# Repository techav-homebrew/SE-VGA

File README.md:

# SE-VGA
SE-VGA is a video card primarily for the Mac SE, but also compatible with the Macintosh, 512k, and Plus. The FPGA configuration here will duplicate the Mac video pixel-doubled to 1024x768 and displayed letterboxed (black borders) in a 1024x768@60Hz frame over VGA. It does this by snooping the CPU bus for writes to the frame buffer region of memory, caching the video data in its own VRAM, and generating a new video signal from that data. It can plug directly into the PDS slot in a Mac SE, or plugs in place of the CPU on the Plus, 512k, or 128k models (CPU must be removed and a socket installed in its place; the CPU must then be installed on the SE-VGA card).

Circuit is built around a Latice iCE40HX4K FPGA with a single 16-bit SDRAM, theoretically supporting up to 512Mbit (64MB) of video memory. Video output is a 24-bit R2R DAC with output buffer. The PCB is designed as a 4-layer board with inner power and ground planes. Use of a PCB assembly service is recommended for the many 0402 passive components. 

The memory capacity and output capabilities of this project greatly exceed those necessary for duplicating the classic Macintosh video output in the hopes that it may be a starting point for projects which go beyond merely duplicating the classic Macintosh video output.

## Bill of Materials

| Qty | Manufacturer    | Part No.           | Name               | Description                                   |
|:---:|:----------------|:-------------------|:-------------------|:----------------------------------------------|
|     |                 |                    |                    |                                               | 

## Frame Buffer Addressing

The Mac primary framebuffer starts at 0x5900 below the top of RAM. Since it's not in a static location for every system, the system's memory configuration is needed. This is set by the Memory Size switches/jumpers. The chart below indicates the primary and alternate frame buffer locations based on the installed SIMM combinations in the Mac Plus/SE, as well as for the 512k & 128k models. 

|Main Framebuffer|Alt Framebuffer|RAM Top Address + 1|RAM Size|Installed SIMMs               |
|:--------------:|:-------------:|:-----------------:|:------:|------------------------------|
| `0x3fa700`     | `0x3f2700`    | `0x400000`        | 4.0MB  | `[ 1MB   1MB ][ 1MB   1MB ]` |
| `0x37a700`     | `0x372700`    | `0x380000`        | 3.5MB  | Invalid combination          |
| `0x2fa700`     | `0x2f2700`    | `0x300000`        | 3.0MB  | Invalid combination          |
| `0x27a700`     | `0x272700`    | `0x280000`        | 2.5MB  | `[ 1MB   1MB ][256kB 256kB]` |
| `0x1fa700`     | `0x1f2700`    | `0x200000`        | 2.0MB  | `[ 1MB   1MB ][ ---   --- ]` |
| `0x17a700`     | `0x172700`    | `0x180000`        | 1.5MB  | Invalid combination          |
| `0x0fa700`     | `0x0f2700`    | `0x100000`        | 1.0MB  | `[256kB 256kB][256kB 256kB]` |
| `0x07a700`     | `0x072700`    | `0x080000`        | 512kB  | `[256kB 256kB][ ---   --- ]` |
| `0x01a700`     | `0x012700`    | `0x020000`        | 128kB  | NA                           |

## FPGA Pin Assignments

|signal|Direction|Pin|
|---|---|---|
|   |   |   |

## Known Issues
- Logic has not yet been rewritten for the iCE40 FPGA

# License
This work is licensed under a Creative Commons Attribution-ShareAlike 4.0 International License. See https://creativecommons.org/licenses/by-sa/4.0/.

# Acknowledgements
Special thanks to TubeTimeUS, whose Graphics Gremlin project answered many of the questions I had while designing this project. 
https://github.com/schlae/graphics-gremlin

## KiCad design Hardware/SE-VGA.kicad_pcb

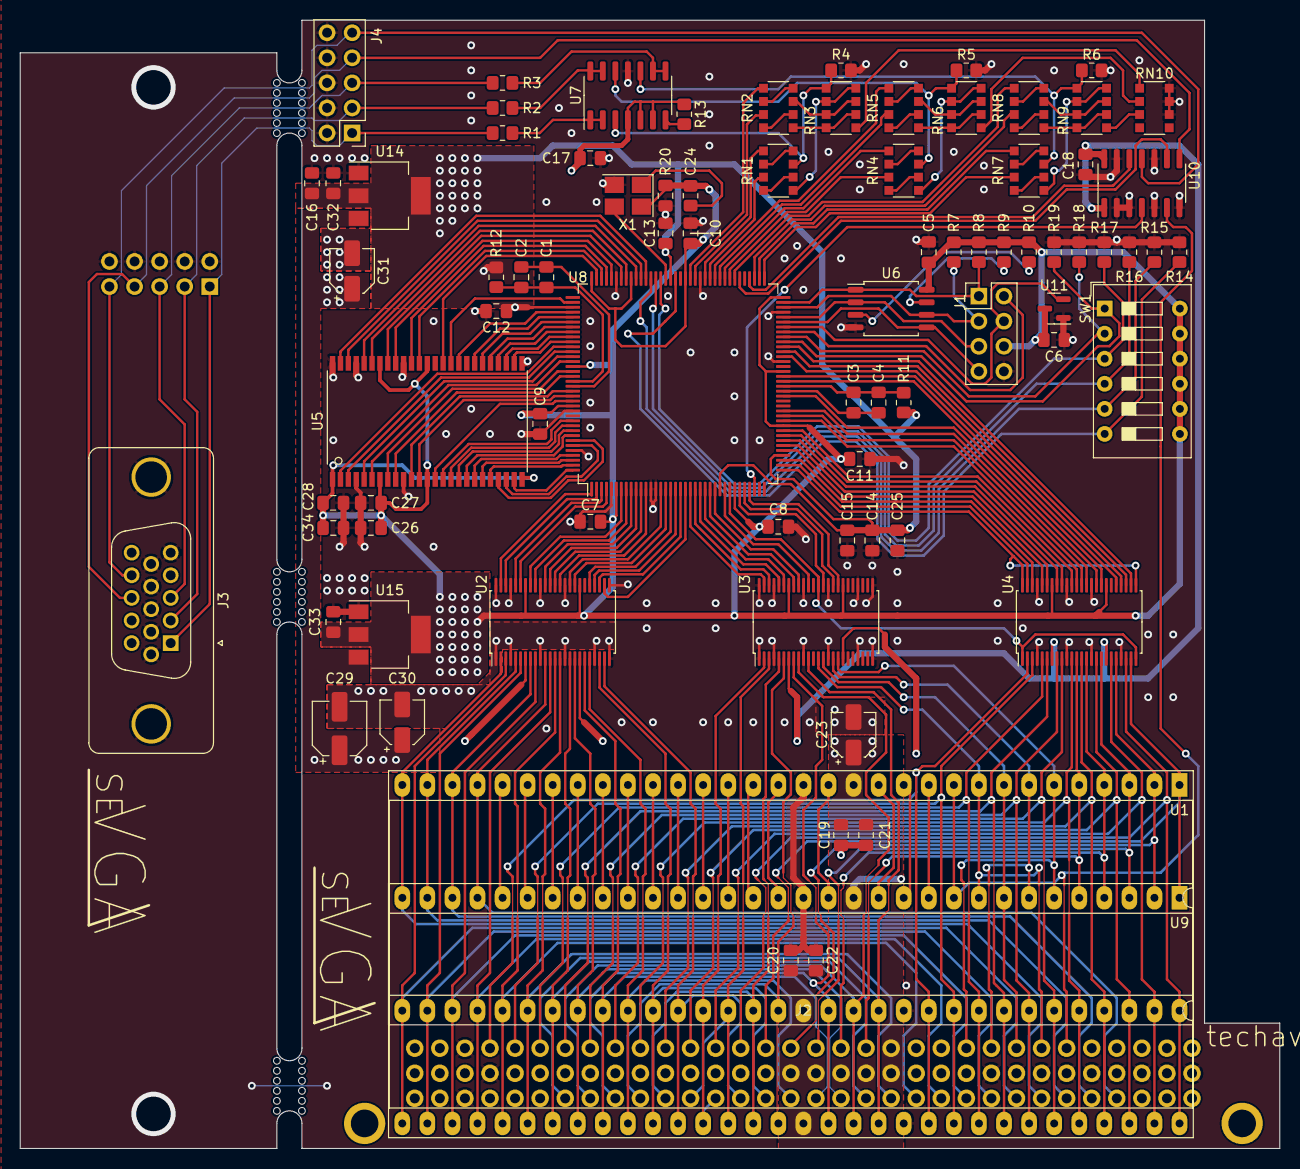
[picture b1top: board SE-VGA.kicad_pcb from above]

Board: 2 copper layers, 127.6 x 114.3 mm, 84 parts (1 on the bottom side), 215 nets.

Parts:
C1, C3, C5, C6, C7, C8, C9, C10, C13, C14, C15, C16, C17, C18, C19, C20, C24, C27, C28: 1uF; C_0805_2012Metric_Pad1.18x1.45mm_HandSolder
C2, C4, C11, C12, C21, C22, C25, C26, C32, C33, C34: 4.7uF; C_0805_2012Metric_Pad1.18x1.45mm_HandSolder
C23, C30, C31: 10uF; CP_Elec_4x5.3
C29: 100uF; CP_Elec_5x5.4
J1: PGM; PinHeader_2x04_P2.54mm_Vertical
J2: 650946-5; DIN41612-32ABC
J3: DE15_Receptacle_HighDensity_MountingHoles; DSUB-15-HD_Female_Vertical_P2.29x1.98mm_MountingHoles
J4, J5: Conn_02x05_Odd_Even; PinHeader_2x05_P2.54mm_Vertical
R1, R2, R3, R4, R5, R6, R13: 75R; R_0805_2012Metric_Pad1.20x1.40mm_HandSolder
R7, R8, R9, R10, R14, R15, R16, R17, R18, R19, R20: 10K; R_0805_2012Metric_Pad1.20x1.40mm_HandSolder
R11, R12: 100; R_0805_2012Metric_Pad1.20x1.40mm_HandSolder
RN1, RN2, RN3, RN4, RN5, RN6, RN7, RN8, RN9, RN10: CAY16-1500F4LF; R_Array_Convex_4x1206
SW1: SW_DIP_x06; SW_DIP_SPSTx06_Slide_9.78x17.42mm_W7.62mm_P2.54mm
U1: 68000-CPU; DIP-64_W22.86mm_Socket_LongPads
U2, U3, U4: SN74LVCH16T245; TSSOP-48_6.1x12.5mm_P0.5mm
U5: IS42S16100H; TSOP2-50
U6: W25Q80DVSNIG; SOIC-8_5.275x5.275mm_P1.27mm
U7: ADA4891-4; SOIC-14_3.9x8.7mm_P1.27mm
U8: ICE40HX4K-TQ144; TQFP-144_20x20mm_P0.5mm
U9: 68000-BOARD; DIP-64_W22.86mm_Socket_LongPads
U10: 74HCT125D; SOIC-14_3.9x8.7mm_P1.27mm
U11: APX803S00-29SA-7; SOT-23
U14: AZ1117IH-1.2TRG1; SOT-223-3_TabPin2
U15: AZ1117IH-3.3TRG1; SOT-223-3_TabPin2
X1: ECS-2333-100-BN-TR; Oscillator_SMD_Abracon_ASE-4Pin_3.2x2.5mm_HandSoldering

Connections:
+1V2: C12.2, C13.2, C14.2, C15.2, C16.2, C25.2, C32.2, R11.2, R12.2, U8.27 (VCC), U8.40 (VCC), U8.92 (VCC), U8.111 (VCC), U14.2 (VO)
+3V3: C5.2, C6.2, C7.2, C8.2, C9.2, C10.2, C11.2, C24.1, C26.2, C27.2, C28.2, C33.2, C34.2, J1.6, R7.2, R8.2, R9.2, R10.2, R20.2, SW1.7, SW1.8, SW1.9, SW1.10, SW1.11, SW1.12, U2.31 (VCCA), U2.42 (VCCA), U3.31 (VCCA), U3.42 (VCCA), U4.31 (VCCA), U4.42 (VCCA), U5.1 (VDD), U5.7 (VDDQ), U5.13 (VDDQ), U5.25 (VDD), U5.38 (VDDQ), U5.44 (VDDQ), U6.8 (VDD), U8.6 (VCCIO_3), U8.30 (VCCIO_3), U8.46 (VCCIO_2), U8.57 (VCCIO_2), U8.72 (VCC_SPI), U8.89 (VCCIO_1), U8.100 (VCCIO_1), U8.108 (VPP_2V5), U8.123 (VCCIO_0), U8.131 (VCCIO_0), U11.3 (VCC), U15.2 (VO), X1.4 (VDD)
+5V: C17.2, C18.2, C19.2, C20.2, C21.2, C22.2, C23.1, C29.1, C30.1, C31.1, J2.B13, J2.B14, J2.B15, J2.B16, J2.B17, J2.C13, R13.1, U1.14 (VCC), U1.49 (VCC), U2.7 (VCCB), U2.18 (VCCB), U3.7 (VCCB), U3.18 (VCCB), U4.7 (VCCB), U4.18 (VCCB), U7.4 (VCC), U7.5 (IN2_P), U7.6 (IN2_N), U9.14 (VCC), U9.49 (VCC), U10.1, U10.14 (VCC), U14.3 (VI), U15.3 (VI)
/AUXSW: R14.2, SW1.6, U8.91 (IOR_139)
/CBSEL0: R19.2, SW1.1, U8.63 (IOB_103_CBSEL0)
/CBSEL1: R18.2, SW1.2, U8.64 (IOB_104_CBSEL1)
/CLK-10M: U8.93 (IOR_140_GBIN3), X1.3 (OUT)
/CPU3-A1: U2.38 (1A7), U8.9 (IOL_5A)
/CPU3-A2: U2.41 (1A5), U8.7 (IOL_4A)
/CPU3-A3: U2.44 (1A3), U8.3 (IOL_3A)
/CPU3-A4: U2.47 (1A1), U8.1 (IOL_2A)
/CPU3-A5: U2.46 (1A2), U8.2 (IOL_2B)
/CPU3-A6: U2.43 (1A4), U8.4 (IOL_3B)
/CPU3-A7: U2.40 (1A6), U8.8 (IOL_4B)
/CPU3-A8: U2.37 (1A8), U8.10 (IOL_5B)
/CPU3-A9: U2.36 (2A1), U8.11 (IOL_8A)
/CPU3-A10: U2.35 (2A2), U8.12 (IOL_8B)
/CPU3-A11: U2.33 (2A3), U8.15 (IOL_10A)
/CPU3-A12: U2.32 (2A4), U8.16 (IOL_10B)
/CPU3-A13: U2.28 (2A5), U8.18 (IOL_12B)
/CPU3-A14: U2.29 (2A6), U8.17 (IOL_12A)
/CPU3-A15: U2.27 (2A7), U8.19 (IOL_13A)
/CPU3-A16: U2.26 (2A8), U8.20 (IOL_13B_GBIN7)
/CPU3-A17: U3.47 (1A1), U8.21 (IOL_14A_GBIN6)
/CPU3-A18: U3.46 (1A2), U8.22 (IOL_14B)
/CPU3-A19: U3.44 (1A3), U8.23 (IOL_17A)
/CPU3-A20: U3.43 (1A4), U8.24 (IOL_17B)
/CPU3-A21: U3.41 (1A5), U8.25 (IOL_18A)
/CPU3-A22: U3.40 (1A6), U8.26 (IOL_18B)
/CPU3-A23: U3.38 (1A7), U8.28 (IOL_23A)
/CPU3-D0: U4.37 (1A8), U8.47 (IOB_79)
/CPU3-D1: U4.35 (2A2), U8.49 (IOB_81_GBIN5)
/CPU3-D2: U4.32 (2A4), U8.55 (IOB_91)
/CPU3-D3: U4.29 (2A6), U8.56 (IOB_94)
/CPU3-D4: U4.26 (2A8), U8.62 (IOB_102)
/CPU3-D5: U4.27 (2A7), U8.61 (IOB_96)
/CPU3-D6: U4.28 (2A5), U8.60 (IOB_95)
/CPU3-D7: U4.33 (2A3), U8.52 (IOB_82_GBIN4)
/CPU3-D8: U4.36 (2A1), U8.48 (IOB_80)
/CPU3-D9: U4.38 (1A7), U8.45 (IOB_73)
/CPU3-D10: U4.40 (1A6), U8.44 (IOB_72)
/CPU3-D11: U4.41 (1A5), U8.43 (IOB_71)
/CPU3-D12: U4.43 (1A4), U8.42 (IOB_64)
/CPU3-D13: U4.44 (1A3), U8.41 (IOB_63)
/CPU3-D14: U4.46 (1A2), U8.39 (IOB_61)
/CPU3-D15: U4.47 (1A1), U8.38 (IOB_57)
/CPU3-R/~W: U3.36 (2A1), U4.1 (1DIR), U4.24 (2DIR), U8.29 (IOL_23B)
/MEMSEL0: R17.2, SW1.3, U8.94 (IOR_141_GBIN2)
/MEMSEL1: R16.2, SW1.4, U8.95 (IOR_144)
/MEMSEL2: R15.2, SW1.5, U8.96 (IOR_146)
/Mac Interface/CPU-A1: J2.A4, U1.29 (A1), U2.11 (1B7), U9.29 (A1)
/Mac Interface/CPU-A2: J2.A5, U1.30 (A2), U2.8 (1B5), U9.30 (A2)
/Mac Interface/CPU-A3: J2.A6, U1.31 (A3), U2.5 (1B3), U9.31 (A3)
/Mac Interface/CPU-A4: J2.A7, U1.32 (A4), U2.2 (1B1), U9.32 (A4)
/Mac Interface/CPU-A5: J2.A8, U1.33 (A5), U2.3 (1B2), U9.33 (A5)
/Mac Interface/CPU-A6: J2.A9, U1.34 (A6), U2.6 (1B4), U9.34 (A6)
/Mac Interface/CPU-A7: J2.A10, U1.35 (A7), U2.9 (1B6), U9.35 (A7)
/Mac Interface/CPU-A8: J2.A11, U1.36 (A8), U2.12 (1B8), U9.36 (A8)
/Mac Interface/CPU-A9: J2.A12, U1.37 (A9), U2.13 (2B1), U9.37 (A9)
/Mac Interface/CPU-A10: J2.A13, U1.38 (A10), U2.14 (2B2), U9.38 (A10)
/Mac Interface/CPU-A11: J2.A14, U1.39 (A11), U2.16 (2B3), U9.39 (A11)
/Mac Interface/CPU-A12: J2.A15, U1.40 (A12), U2.17 (2B4), U9.40 (A12)
/Mac Interface/CPU-A13: J2.A16, U1.41 (A13), U2.19 (2B5), U9.41 (A13)
/Mac Interface/CPU-A14: J2.A17, U1.42 (A14), U2.20 (2B6), U9.42 (A14)
/Mac Interface/CPU-A15: J2.A18, U1.43 (A15), U2.22 (2B7), U9.43 (A15)
/Mac Interface/CPU-A16: J2.A19, U1.44 (A16), U2.23 (2B8), U9.44 (A16)
/Mac Interface/CPU-A17: J2.A20, U1.45 (A17), U3.2 (1B1), U9.45 (A17)
/Mac Interface/CPU-A18: J2.A21, U1.46 (A18), U3.3 (1B2), U9.46 (A18)
/Mac Interface/CPU-A19: J2.A22, U1.47 (A19), U3.5 (1B3), U9.47 (A19)
/Mac Interface/CPU-A20: J2.A23, U1.48 (A20), U3.6 (1B4), U9.48 (A20)
/Mac Interface/CPU-A21: J2.A24, U1.50 (A21), U3.8 (1B5), U9.50 (A21)
/Mac Interface/CPU-A22: J2.A25, U1.51 (A22), U3.9 (1B6), U9.51 (A22)
/Mac Interface/CPU-A23: J2.A26, U1.52 (A23), U3.11 (1B7), U9.52 (A23)
/Mac Interface/CPU-CLK: U1.15 (CLK), U9.15 (CLK)
/Mac Interface/CPU-D0: J2.C14, U1.5 (D0), U4.12 (1B8), U9.5 (D0)
/Mac Interface/CPU-D1: J2.C15, U1.4 (D1), U4.14 (2B2), U9.4 (D1)
/Mac Interface/CPU-D2: J2.C16, U1.3 (D2), U4.17 (2B4), U9.3 (D2)
/Mac Interface/CPU-D3: J2.C17, U1.2 (D3), U4.20 (2B6), U9.2 (D3)
/Mac Interface/CPU-D4: J2.C18, U1.1 (D4), U4.23 (2B8), U9.1 (D4)
/Mac Interface/CPU-D5: J2.C19, U1.64 (D5), U4.22 (2B7), U9.64 (D5)
/Mac Interface/CPU-D6: J2.C20, U1.63 (D6), U4.19 (2B5), U9.63 (D6)
/Mac Interface/CPU-D7: J2.C21, U1.62 (D7), U4.16 (2B3), U9.62 (D7)
/Mac Interface/CPU-D8: J2.C22, U1.61 (D8), U4.13 (2B1), U9.61 (D8)
/Mac Interface/CPU-D9: J2.C23, U1.60 (D9), U4.11 (1B7), U9.60 (D9)
/Mac Interface/CPU-D10: J2.C24, U1.59 (D10), U4.9 (1B6), U9.59 (D10)
/Mac Interface/CPU-D11: J2.C25, U1.58 (D11), U4.8 (1B5), U9.58 (D11)
/Mac Interface/CPU-D12: J2.C26, U1.57 (D12), U4.6 (1B4), U9.57 (D12)
/Mac Interface/CPU-D13: J2.C27, U1.56 (D13), U4.5 (1B3), U9.56 (D13)
/Mac Interface/CPU-D14: J2.C28, U1.55 (D14), U4.3 (1B2), U9.55 (D14)
/Mac Interface/CPU-D15: J2.C29, U1.54 (D15), U4.2 (1B1), U9.54 (D15)
/Mac Interface/CPU-E: U1.20 (E), U9.20 (E)
/Mac Interface/CPU-FC0: U1.28 (FC0), U9.28 (FC0)
/Mac Interface/CPU-FC1: U1.27 (FC1), U9.27 (FC1)
/Mac Interface/CPU-FC2: U1.26 (FC2), U9.26 (FC2)
/Mac Interface/CPU-R/~W: J2.C7, U1.9 (R/W), U3.13 (2B1), U9.9 (R/W)
/Mac Interface/~CPU-AS: J2.C10, U1.6 (AS), U3.17 (2B4), U9.6 (AS)
/Mac Interface/~CPU-BERR: U1.22 (BERR), U9.22 (BERR)
/Mac Interface/~CPU-BGACK: U1.12 (BGACK), U9.12 (BGACK)
/Mac Interface/~CPU-BG: U1.11 (BG), U9.11 (BG)
/Mac Interface/~CPU-BR: U1.13 (BR), U9.13 (BR)
/Mac Interface/~CPU-HALT: U1.17 (HALT), U9.17 (HALT)
/Mac Interface/~CPU-IPL0: U1.25 (IPL0), U9.25 (IPL0)
/Mac Interface/~CPU-IPL1: U1.24 (IPL1), U9.24 (IPL1)
/Mac Interface/~CPU-IPL2: U1.23 (IPL2), U9.23 (IPL2)
/Mac Interface/~CPU-LDS: J2.C8, U1.8 (LDS), U3.14 (2B2), U9.8 (LDS)
/Mac Interface/~CPU-RESET: U1.18 (RESET), U9.18 (RESET)
/Mac Interface/~CPU-UDS: J2.C9, U1.7 (UDS), U3.16 (2B3), U9.7 (UDS)
/Mac Interface/~CPU-VMA: U1.19 (VMA), U9.19 (VMA)
/Mac Interface/~CPU-VPA: U1.21 (VPA), U9.21 (VPA)
/SPI_SCK: J1.3, R7.1, U6.6 (SCK), U8.70 (IOB_107_SCK)
/SPI_SDI: J1.5, U6.2 (SO), U8.68 (IOB_106_SDI)
/SPI_SDO: J1.7, U6.5 (SI), U8.67 (IOB_105_SDO)
/SPI_SS: J1.1, R8.1, U6.1 (~CE), U8.71 (IOB_108_SS)
/VID-B0: RN8.3 (R3.1), U8.75 (IOR_111)
/VID-B1: RN8.1 (R1.1), U8.79 (IOR_115)
/VID-B2: RN7.3 (R3.1), U8.73 (IOR_109)
/VID-B3: RN7.1 (R1.1), U8.74 (IOR_110)
/VID-B-A: J3.3, J4.5, J5.5, R3.2
/VID-G0: RN5.3 (R3.1), U8.82 (IOR_118)
/VID-G1: RN5.1 (R1.1), U8.83 (IOR_119)
/VID-G2: RN4.3 (R3.1), U8.80 (IOR_116)
/VID-G3: RN4.1 (R1.1), U8.81 (IOR_117)
/VID-G-A: J3.2, J4.3, J5.3, R2.2
/VID-HSYNC: J3.13, J4.7, J5.7, U10.8
/VID-HSYNC3: U8.78 (IOR_114), U10.9
/VID-R0: RN2.3 (R3.1), U8.87 (IOR_136)
/VID-R1: RN2.1 (R1.1), U8.88 (IOR_137)
/VID-R2: RN1.3 (R3.1), U8.84 (IOR_120)
/VID-R3: RN1.1 (R1.1), U8.85 (IOR_128)
/VID-R-A: J3.1, J4.1, J5.1, R1.2
/VID-VSYNC: J3.14, J4.9, J5.9, U10.11
/VID-VSYNC3: U8.76 (IOR_112), U10.12
/VRAM-A0: U5.21 (A0), U8.143 (IOT_221)
/VRAM-A1: U5.22 (A1), U8.138 (IOT_216)
/VRAM-A2: U5.23 (A2), U8.139 (IOT_217)
/VRAM-A3: U5.24 (A3), U8.144 (IOT_222)
/VRAM-A4: U5.27 (A4), U8.118 (IOT_177)
/VRAM-A5: U5.28 (A5), U8.117 (IOT_174)
/VRAM-A6: U5.29 (A6), U8.116 (IOT_173)
/VRAM-A7: U5.30 (A7), U8.115 (IOT_172)
/VRAM-A8: U5.31 (A8), U8.114 (IOT_171)
/VRAM-A9: U5.32 (A9), U8.113 (IOT_170)
/VRAM-A10: U5.20 (A10), U8.142 (IOT_220)
/VRAM-A11: U5.19 (A11), U8.141 (IOT_219)
/VRAM-CKE: U5.34 (CKE), U8.112 (IOT_169)
/VRAM-CLK: U5.35 (CLK), U8.110 (IOT_168)
/VRAM-D0: U5.2 (DQ0), U8.119 (IOT_178)
/VRAM-D1: U5.3 (DQ1), U8.120 (IOT_179)
/VRAM-D2: U5.5 (DQ2), U8.121 (IOT_181)
/VRAM-D3: U5.6 (DQ3), U8.122 (IOT_190)
/VRAM-D4: U5.8 (DQ4), U8.124 (IOT_191)
/VRAM-D5: U5.9 (DQ5), U8.125 (IOT_192)
/VRAM-D6: U5.11 (DQ6), U8.128 (IOT_197_GBIN1)
/VRAM-D7: U5.12 (DQ7), U8.129 (IOT_198_GBIN0)
/VRAM-D8: U5.39 (DQ8), U8.106 (IOR_166)
/VRAM-D9: U5.40 (DQ9), U8.105 (IOR_165)
/VRAM-D10: U5.42 (DQ10), U8.104 (IOR_164)
/VRAM-D11: U5.43 (DQ11), U8.102 (IOR_161)
/VRAM-D12: U5.45 (DQ12), U8.101 (IOR_160)
/VRAM-D13: U5.46 (DQ13), U8.99 (IOR_152)
/VRAM-D14: U5.48 (DQ14), U8.98 (IOR_148)
/VRAM-D15: U5.49 (DQ15), U8.97 (IOR_147)
/VRAM-LDQM: U5.14 (LDQM), U8.130 (IOT_206)
/VRAM-UDQM: U5.36 (UDQM), U8.107 (IOR_167)
/~CDONE: J1.2, U8.65 (CDONE)
/~CPU3-AS: U3.32 (2A4), U8.33 (IOL_25A)
/~CPU3-DEN: U4.25 (~2OE), U4.48 (~1OE), U8.37 (IOB_56)
/~CPU3-DTACK: U8.34 (IOL_25B), U10.4
/~CPU3-LDS: U3.35 (2A2), U8.31 (IOL_24A)
/~CPU3-UDS: U3.33 (2A3), U8.32 (IOL_24B)
/~CPU-DTACK: J2.C6, U1.10 (DTACK), U9.10 (DTACK), U10.6
/~CRESET: J1.4, U8.66 (~CRESET), U11.2 (~RESET)
/~VRAM-CAS: U5.16 (~CAS), U8.135 (IOT_213)
/~VRAM-CS: U5.18 (~CS), U8.137 (IOT_215)
/~VRAM-RAS: U5.17 (~RAS), U8.136 (IOT_214)
/~VRAM-WE: U5.15 (~WE), U8.134 (IOT_212)
GND: C5.1, C6.1, C7.1, C8.1, C9.1, C10.1, C11.1, C12.1, C13.1, C14.1, C15.1, C16.1, C17.1, C18.1, C19.1, C20.1, C21.1, C22.1, C23.2, C24.2, C25.1, C26.1, C27.1, C28.1, C29.2, C30.2, C31.2, C32.1, C33.1, C34.1, J1.8, J2.A30, J2.B1, J2.B2, J2.B3, J2.B4, J2.B5, J2.B6, J2.B7, J2.B8, J2.B9, J2.B29, J2.C30, J3.0, J3.5, J3.6, J3.7, J3.8, J3.9, J3.10, J4.2, J4.4, J4.6, J4.8, J4.10, J5.2, J5.4, J5.6, J5.8, J5.10, R4.1, R5.1, R6.1, R14.1, R15.1, R16.1, R17.1, R18.1, R19.1, RN10.6 (R3.2), RN10.7 (R2.2), RN10.8 (R1.2), U1.16 (GND), U1.53 (GND), U2.1 (1DIR), U2.4 (GND), U2.10 (GND), U2.15 (GND), U2.21 (GND), U2.24 (2DIR), U2.25 (~2OE), U2.34 (GND), U2.39 (GND), U2.45 (GND), U2.48 (~1OE), U3.1 (1DIR), U3.4 (GND), U3.10 (GND), U3.15 (GND), U3.21 (GND), U3.24 (2DIR), U3.25 (~2OE), U3.28 (GND), U3.34 (GND), U3.39 (GND), U3.45 (GND), U3.48 (~1OE), U4.4 (GND), U4.10 (GND), U4.15 (GND), U4.21 (GND), U4.34 (GND), U4.39 (GND), U4.45 (GND), U5.4 (GNDQ), U5.10 (GNDQ), U5.26 (GND), U5.41 (GNDQ), U5.47 (GNDQ), U5.50 (GND), U6.4 (VSS), U7.11 (GND), U8.5 (GND), U8.13 (GND), U8.14 (GND), U8.59 (GND), U8.69 (GND), U8.86 (GND), U8.103 (GND), U8.132 (GND), U8.140 (GND), U9.16 (GND), U9.53 (GND), U10.2, U10.3, U10.5, U10.7 (GND), U10.10, U10.13, U11.1 (GND), U14.1 (GND), U15.1 (GND), X1.2 (GND)
unnamed: RN1.2 (R2.1), RN1.8 (R1.2)
unnamed: R4.2, RN1.7 (R2.2), RN3.1 (R1.1), U7.3 (IN1_P)
unnamed: RN1.4 (R4.1), RN1.6 (R3.2)
unnamed: RN1.5 (R4.2), RN3.2 (R2.1), RN3.8 (R1.2)
unnamed: RN2.2 (R2.1), RN2.8 (R1.2)
unnamed: RN2.7 (R2.2), RN3.3 (R3.1), RN3.7 (R2.2)
unnamed: RN2.4 (R4.1), RN2.6 (R3.2)
unnamed: RN2.5 (R4.2), RN3.4 (R4.1), RN3.6 (R3.2)
unnamed: RN4.2 (R2.1), RN4.8 (R1.2)
unnamed: R5.2, RN4.7 (R2.2), RN6.1 (R1.1), U7.12 (IN4_P)
unnamed: RN4.4 (R4.1), RN4.6 (R3.2)
unnamed: RN4.5 (R4.2), RN6.2 (R2.1), RN6.8 (R1.2)
unnamed: RN5.2 (R2.1), RN5.8 (R1.2)
unnamed: RN5.7 (R2.2), RN6.3 (R3.1), RN6.7 (R2.2)
unnamed: RN5.4 (R4.1), RN5.6 (R3.2)
unnamed: RN5.5 (R4.2), RN6.4 (R4.1), RN6.6 (R3.2)
unnamed: RN7.2 (R2.1), RN7.8 (R1.2)
unnamed: R6.2, RN7.7 (R2.2), RN9.1 (R1.1), U7.10 (IN3_P)
unnamed: RN7.4 (R4.1), RN7.6 (R3.2)
unnamed: RN7.5 (R4.2), RN9.2 (R2.1), RN9.8 (R1.2)
unnamed: RN8.2 (R2.1), RN8.8 (R1.2)
unnamed: RN8.7 (R2.2), RN9.3 (R3.1), RN9.7 (R2.2)
unnamed: RN8.4 (R4.1), RN8.6 (R3.2)
unnamed: RN8.5 (R4.2), RN9.4 (R4.1), RN9.6 (R3.2)
unnamed: RN3.5 (R4.2), RN10.1 (R1.1)
unnamed: RN6.5 (R4.2), RN10.2 (R2.1)
unnamed: RN9.5 (R4.2), RN10.3 (R3.1)
unnamed: R9.1, U6.7 (~HOLD)
unnamed: R10.1, U6.3 (~WP)
unnamed: R1.1, U7.1 (OUT1), U7.2 (IN1_N)
unnamed: R13.2, U7.7 (OUT2)
unnamed: R3.1, U7.8 (OUT3), U7.9 (IN3_N)
unnamed: R2.1, U7.13 (IN4_N), U7.14 (OUT4)
unnamed: C3.1, C4.1, U8.53 (GNDPLL0)
unnamed: C1.1, C2.1, U8.127 (GNDPLL1)
unnamed: C3.2, C4.2, R11.1, U8.54 (VCCPLL0)
unnamed: C1.2, C2.2, R12.1, U8.126 (VCCPLL1)
unnamed: R20.1, X1.1 (Tri-State)

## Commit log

2021-04-07 partial draft 1
2021-04-08 partial draft 2
2021-04-12 First compile
2021-04-13 New output stage
2021-04-17 CPU cycle state machine
2021-04-18 CPU Cycle Improvements 1
2021-04-18 CPU Cycle Improvements 2
2021-04-18 Getting ready for a large refactor
2021-04-18 Refactor Video Out Sequence
2021-04-18 Documentation Cleanup
2021-04-20 Add Alternate Frame Buffer Support
2021-04-20 Pin Assignments
2021-05-15 First Run
    First live tests on actual hardware
2021-05-16 Debugging CPU Bus Snooping
2021-05-22 CPU Snoop Fixes
    Fix for VRAM writes sometimes overlapping VRAM reads
2021-05-22 Add Gerbers
2021-05-24 Preprep for iCE40
2021-06-05 Add Compiled CPLD Configuration
    Both the .pof for Altera CPLD and .jed for Atmel CPLD
2021-07-25 Revert "Preprep for iCE40"
    This reverts commit 0b2eb362d8cf5fd488feb41270f10fc7da9430fc.
2021-07-25 XGA Board Rev
    Rework of board to add support for pixel-doubled image on XGA resolution frame, and installation in Plus or 512k
2021-07-27 Change multiplier part
    Changed 512MLF to 511MLF due to EOL
2021-08-05 Start logic rebuild for XGA
    Ground-up rewrite of the video timing and output logic for XGA. Much simpler than the initial VGA logic. First draft, incomplete.
2021-10-07 Starting new cpu snoop
2021-10-08 CPU Snoop First Draft
2021-10-08 VIA snooping
2021-10-09 Debugging VRAM Write Timing
2021-10-11 New State Machine
2021-10-12 Rebuilt state machine again
2021-10-13 Fixed image overwrite issues
2021-10-17 Cleanup
2021-10-17 Another fresh start
2021-10-17 Rewrite again
2021-10-23 Mostly working
2021-10-23 Cleanup old logic
2023-06-29 Rev3 Initial Schematic
2023-06-30 R3 Initial schematic complete, start routing
2023-07-01 R3 PCB layout first draft
2023-07-14 Multiplex CPU bus and add 24bpp output
2023-07-14 Cleanup for DRC
2023-07-14 Add CC-BY-SA license and initial Rev3 Readme
2023-07-14 Add initial PCB render
2023-07-14 Upload new schematic plot
2023-07-14 Clean out old gerbers
2023-07-14 Clean out old compiled logic
